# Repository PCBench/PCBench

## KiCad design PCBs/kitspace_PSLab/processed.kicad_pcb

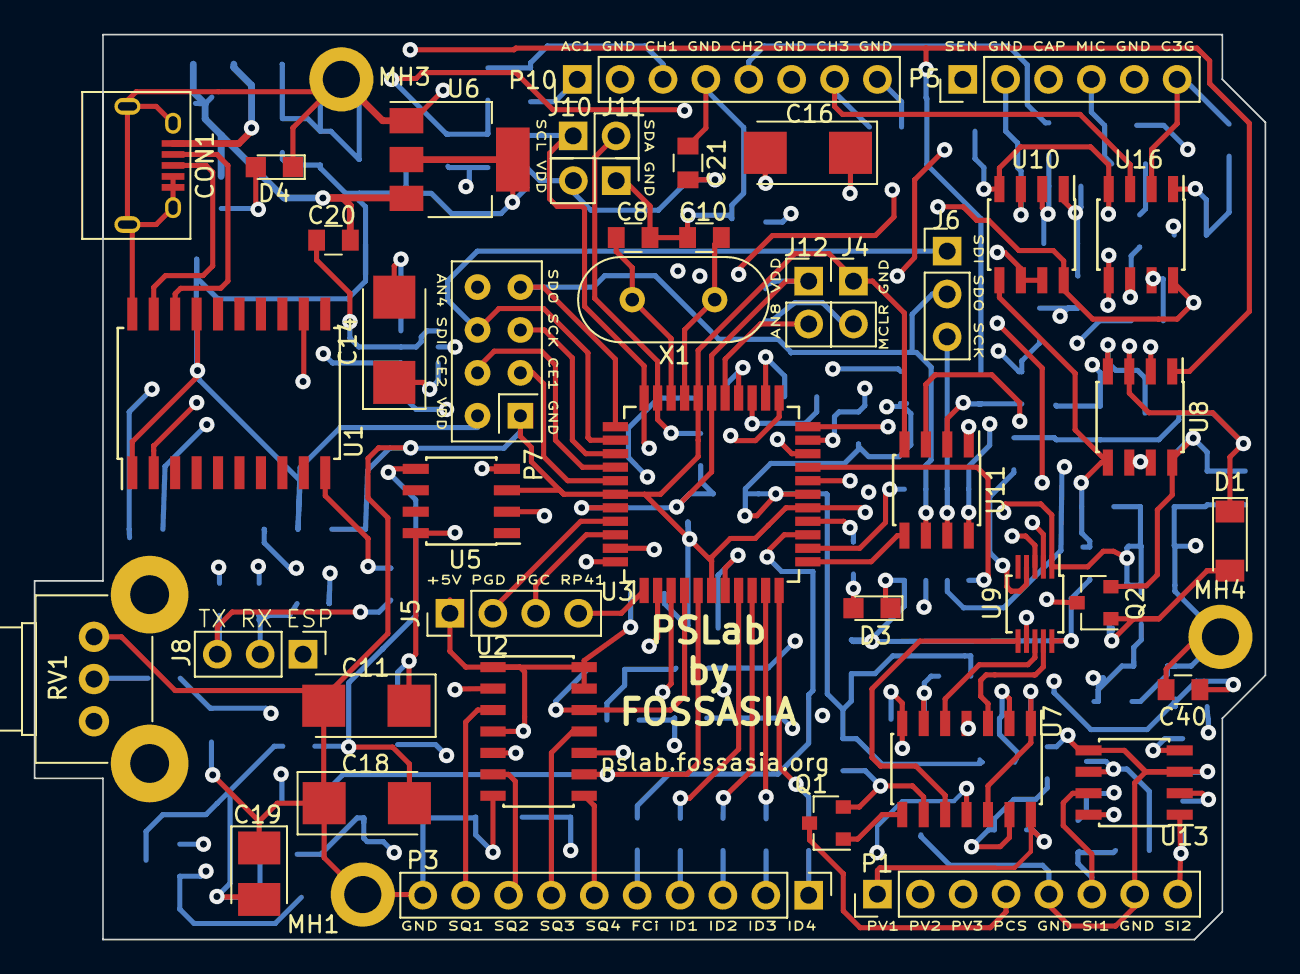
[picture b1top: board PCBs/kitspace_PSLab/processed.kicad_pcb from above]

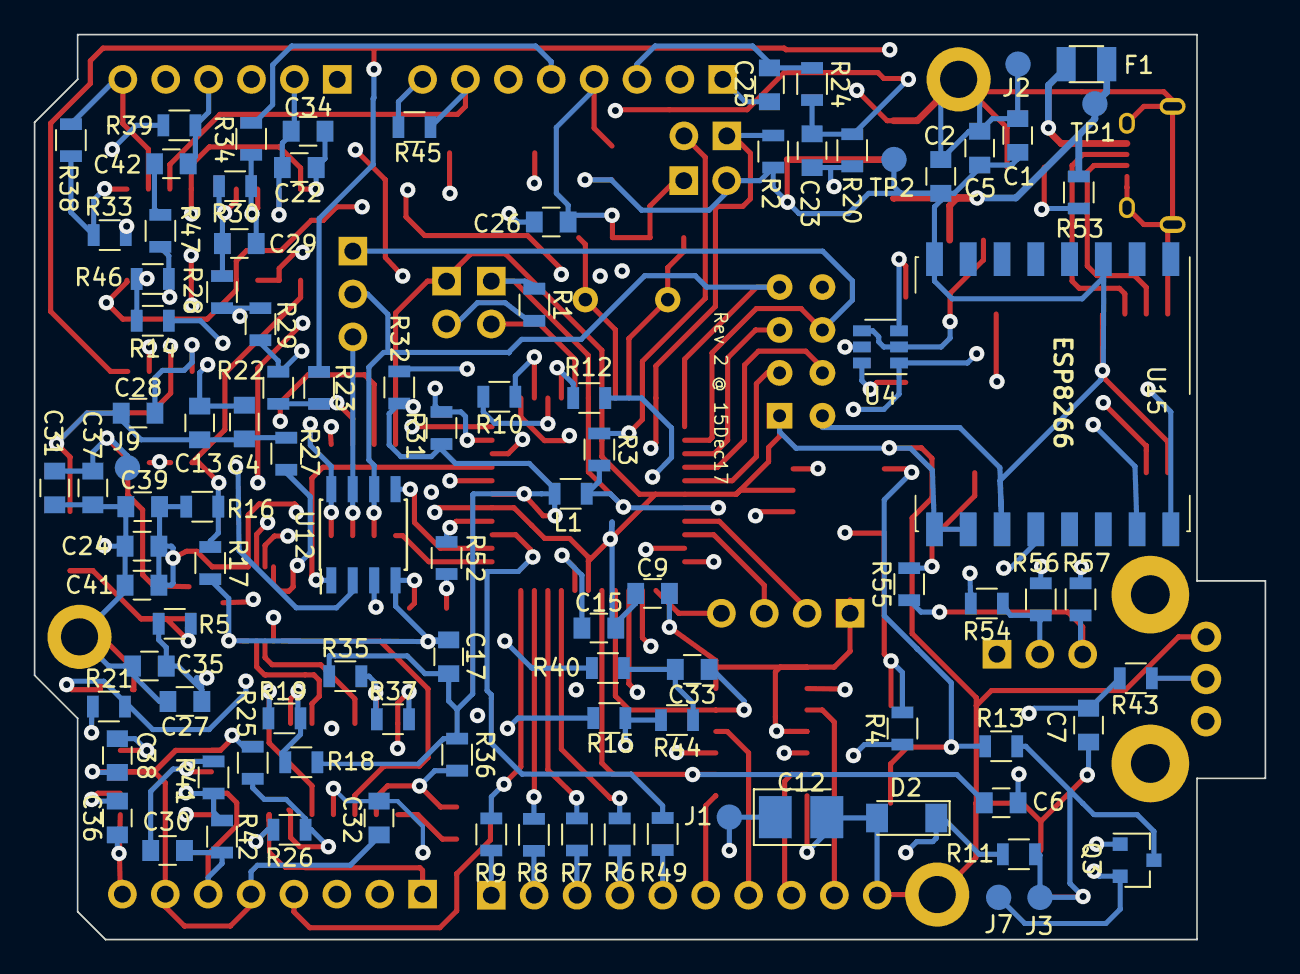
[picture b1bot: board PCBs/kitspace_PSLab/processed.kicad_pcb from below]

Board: 4 copper layers, 72.9 x 53.6 mm, 144 parts (99 on the bottom side), 114 nets.

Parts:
C1, C2, C4, C5, C9, C13, C17, C22, C24, C25, C26, C27, C28, C31, C32, C34, C35, C37, C38, C39, C41: 0.1u; C_0805
C6, C15, C21, C33: 10u; C_0805
C7, C40: 10nF; C_0805
C8, C10: 15pF; C_0805
C11, C14, C16, C18: 100u; CP_Tantalum_Case-C_EIA-6032-28_Reflow
C12, C19: 33u; CP_Tantalum_Case-B_EIA-3528-21_Reflow
C20, C42: 1u; C_0805
C23, C29: 3p3; C_0805
C30, C36: 1nF; C_0805
CON1: USB-MICRO-B; USB_Micro-B
D1, D2: 6V8; D_MiniMELF
D3, D4: LED; LED_0805
F1: 0.5A; Fuse_SMD1206_Reflow
J1: V+; Measurement_Point_Round-SMD-Pad_Small
J2: GND; Measurement_Point_Round-SMD-Pad_Small
J3: V-; Measurement_Point_Round-SMD-Pad_Small
J4: Ex-I; Pin_Header_Straight_1x02_Pitch2.54mm
J5: PG_Pins; Pin_Header_Straight_1x04_Pitch2.54mm
J6: Exp; Pin_Header_Straight_1x03_Pitch2.54mm
J7: VR-; Measurement_Point_Round-SMD-Pad_Small
J8: TX_RX_ES; Pin_Header_Straight_1x03_Pitch2.54mm
J9: VR+; Measurement_Point_Round-SMD-Pad_Small
J10: I2C-I; Pin_Header_Straight_1x02_Pitch2.54mm
J11: I2C-II; Pin_Header_Straight_1x02_Pitch2.54mm
J12: Ex-II; Pin_Header_Straight_1x02_Pitch2.54mm
L1: 10uH; L_0805
MH1, MH3, MH4: M; MountingHole_2.2mm_M2_ISO14580_Pad
P1: CONN_01X08; Pin_Header_Straight_1x08_Pitch2.54mm
P3: DIO; Pin_Header_Straight_1x10_Pitch2.54mm
P5: sen-cap; Pin_Header_Straight_1x06_Pitch2.54mm
P7: NRF; nRF24L01_Breakout_2
P10: Analog; Pin_Header_Straight_1x08_Pitch2.54mm
Q1, Q3: MMBT3906; SOT-23
Q2: MMBT3904; SOT-23
R1, R2, R3, R10, R14, R16, R17, R18, R19, R21, R22, R23, R25, R28, R29, R31, R32, R33, R35, R37, R38, R39, R42: 10K; R_0805
R4, R13, R54, R55, R56, R57: 18; R_0805
R5, R11, R27, R36, R47: 1K; R_0805
R6, R7, R8, R9: 200; R_0805
R12, R15, R26, R41, R43, R44, R52, R53: 5K1; R_0805
R20, R30, R40, R46: 200K; R_0805
R24, R34, R45: 1M; R_0805
R49: 560; R_0805
RV1: 47K; Potentiometer_Alps_RK09K_Vertical
TP1: 5V; Measurement_Point_Round-SMD-Pad_Small
TP2: Vdd; Measurement_Point_Round-SMD-Pad_Small
U1: MCP2200; SOIC-20W_7.5x12.8mm_Pitch1.27mm
U2: 74HC126; SOIC-14_3.9x8.7mm_Pitch1.27mm
U3: PIC24EP256GP204; TQFP-44_10x10mm_Pitch0.8mm
U4: TC1240A; SOT-23-6
U5: 7660; SOIC-8_3.9x4.9mm_Pitch1.27mm
U6: LM1117-3.3; SOT-223
U7: LM324; SOIC-14_3.9x8.7mm_Pitch1.27mm
U8, U10, U13, U16: TL082; SOIC-8_3.9x4.9mm_Pitch1.27mm
U9: MCP4728; MSOP-10_3x3mm_Pitch0.5mm
U11, U12: 6S21; SOIC-8_3.9x4.9mm_Pitch1.27mm
U15: ESP8266; Hopref_RFM9XW_SMD
X1: 12MHz; Crystal_HC49-U_Vertical

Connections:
12MHz: C8.2, U1.2, U3.31, X1.1
+5V: C9.2, C20.2, F1.2, J5.1, R53.2, TP1.1, U2.1, U2.4, U2.10, U2.13, U2.14, U4.1, U6.3
/CAP: P5.3, R10.1, U3.24
/D+: CON1.3, U1.19
/D-: CON1.2, U1.18
/ERxD: R56.1, U15.15
/ESPROG: J8.1, U15.12
/ETxD: R57.1, U15.16
/FCin: P3.5, R49.2
/I/O Processing/DAC1: U7.3, U9.9
/I/O Processing/DAC2: U7.5, U9.8
/I/O Processing/DAC4: U7.10, U9.6
/ID1: R6.2, U3.8
/ID2: R7.2, U3.9
/ID3: R8.2, U3.10
/ID4: R9.2, U3.11
/MCLR: J4.2, R1.2, U3.18
/MRxD: R54.2, U1.12
/MTxD: R55.2, U1.10
/RxD: J8.2, R54.1, R56.2, U3.43
/SEN: P5.1, R12.1, U3.26
/SQR1: P3.9, U2.3
/SQR2: P3.8, U2.6
/SQR3: P3.7, U2.11
/SQR4: P3.6, U2.8
/TxD: J8.3, R55.1, R57.2, U3.44
ACH1: C25.2, P10.1
AN4: P7.8, U3.23
AN8: J12.2, U3.27
AVdd: C17.2, C24.2, C39.2, C41.2, L1.1, R12.2, R16.2, R18.1, R22.2, R29.1, R31.2, R32.2, R35.1, R36.1, R39.2, U3.17, U9.1, U11.8, U12.8
CH1: C25.1, P10.3, R24.1
CH1out: U3.22, U11.1
CH2: P10.5, R34.1
CH2out: U3.19, U12.1
CH3: P10.7, R45.2, U16.3
CH3.GAIN: P5.6, R38.1, U16.2
CH3out: R32.1, R33.1, U3.20
CS.CH1: U3.12, U11.5
CS.CH2: U3.13, U12.5
CS.E1: P7.3, U3.38
CS.E2: P7.4, U3.37
GND: C1.2, C2.1, C4.2, C5.2, C7.2, C8.1, C9.1, C10.1, C11.2, C12.2, C13.1, C15.2, C17.1, C18.1, C19.1, C20.1, C21.2, C22.1, C24.1, C26.1, C27.2, C28.1, C31.1, C32.2, C34.1, C35.1, C37.1, C38.1, C39.1, C40.2, C41.1, CON1.4, CON1.5, CON1.6, D1.1, D2.2, D3.1, D4.1, J2.1, J4.1, J11.1, MH1.1, MH3.1, MH4.1, P1.5, P1.7, P3.10, P5.2, P5.5, P7.1, P10.2, P10.4, P10.6, P10.8, R17.2, R25.1, R27.2, R40.2, R45.1, RV1.1, U1.20, U2.7, U3.6, U3.16, U3.29, U3.39, U4.2, U4.4, U5.3, U6.1, U8.3, U9.10, U10.3, U11.4, U12.4, U13.3, U13.5, U15.9, U15.10, U16.5
MIC: C42.2, P5.4, R39.1
MICout: R14.1, R31.1, U3.21
unnamed: C6.2, RV1.3
unnamed: C7.1, R41.2, R42.1, R43.2
unnamed: C10.2, U3.30, X1.2
unnamed: C11.1, R4.2, U4.5, U5.8
unnamed: C14.1, U4.6
unnamed: C14.2, U4.3
unnamed: C15.1, U3.7
unnamed: C16.1, U5.2
unnamed: C16.2, U5.4
unnamed: C18.2, R13.2, U5.5
unnamed: C23.1, R20.1, R23.2, U8.1
unnamed: C23.2, R20.2, R24.2, U8.2
unnamed: C29.1, R28.1, R30.1, U10.1
unnamed: C29.2, R30.2, R34.2, U10.2
unnamed: C30.2, R41.1, U13.6
unnamed: C33.2, R40.1, R44.1
unnamed: C36.2, R15.1, U13.2
unnamed: C40.1, R15.2, R21.2, R44.2
unnamed: C42.1, R47.2
unnamed: CON1.1, F1.1
unnamed: D1.2, Q2.1, R5.2
unnamed: D2.1, Q3.1, R11.1
unnamed: D3.2, R52.1
unnamed: D4.2, R53.1
unnamed: P3.1, R9.1
unnamed: P3.2, R8.1
unnamed: P3.3, R7.1
unnamed: P3.4, R6.1
unnamed: Q1.1, U7.8
unnamed: Q1.2, R36.2, U7.9
unnamed: R10.2, U3.25
unnamed: R14.2, R46.2, U16.7
unnamed: R16.1, R17.1, U8.5, U10.5
unnamed: R18.2, R19.1, U7.2
unnamed: R19.2, U7.1, U7.12
unnamed: R22.1, R23.1, U11.2
unnamed: R25.2, R26.1, U7.13
unnamed: R27.1, U9.4
unnamed: R28.2, R29.2, U12.2
unnamed: R33.2, R38.2, U16.1
unnamed: R35.2, R37.1, U7.6
unnamed: R43.1, RV1.2
unnamed: R46.1, R47.1, U16.6
unnamed: R49.1, U3.14
unnamed: U2.2, U3.2
unnamed: U2.5, U3.3
unnamed: U10.6, U10.7, U12.3
unnamed: U8.6, U8.7, U11.3
PCS: P1.4, Q1.3
PGC2: J5.3, U3.42
PGD2: J5.2, U3.41
PVS1: P1.1, R26.2, U7.14
PVS2: P1.2, R37.2, U7.7
PVS3: P1.3, U9.7
RP41: J5.4, U3.1
RP147: R52.2, U3.15
SCK: J6.3, P7.5, U3.36, U11.7, U12.7
SCL: J10.1, R2.1, U3.33, U9.2
SDA: J10.2, R3.1, U3.32, U9.3
SDI: J6.1, P7.6, U3.35
SDO: J6.2, P7.7, U3.34, U11.6, U12.6
SINE1: C30.1, P1.6, R42.2, U13.7
SINE2: C36.1, P1.8, R21.1, U13.1
SQ3: C33.1, U2.12, U3.4
SQ4: C6.1, U2.9, U3.5
V+: C12.1, C27.1, C35.2, J1.1, Q2.3, R4.1, R5.1, U7.4, U13.8
V-: C19.2, C32.1, C38.2, J3.1, Q3.3, R11.2, R13.1, U7.11, U13.4
VR+: C26.2, C31.2, C37.2, J9.1, Q2.2, U8.8, U10.8, U16.8
VR-: C22.2, C28.2, C34.2, J7.1, Q3.2, U8.4, U10.4, U16.4
Vdd: C1.1, C2.2, C4.1, C5.1, C13.2, C21.1, J11.2, J12.1, L1.2, P7.2, R1.1, R2.2, R3.2, TP2.1, U1.1, U1.17, U3.28, U3.40, U6.2, U6.4, U15.3, U15.8, U15.11

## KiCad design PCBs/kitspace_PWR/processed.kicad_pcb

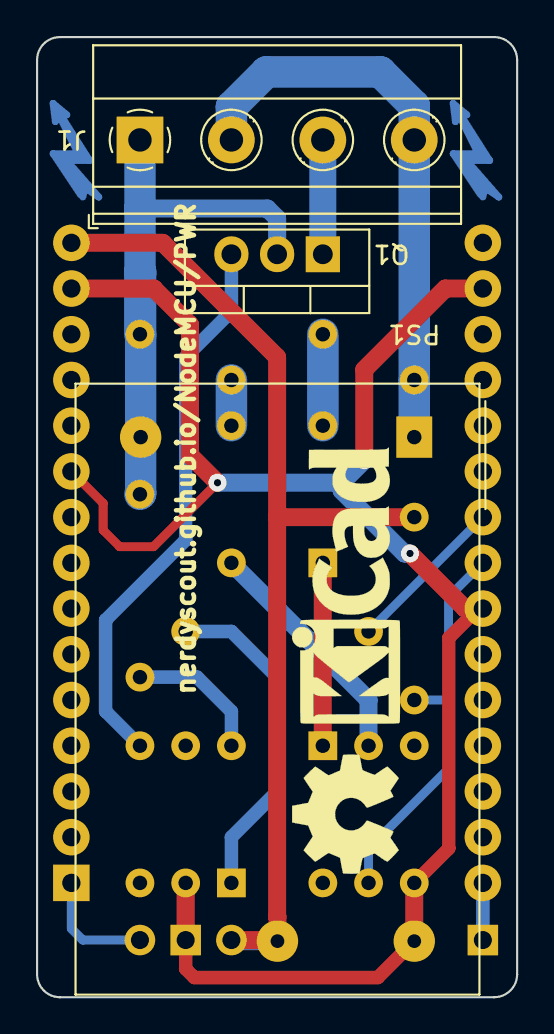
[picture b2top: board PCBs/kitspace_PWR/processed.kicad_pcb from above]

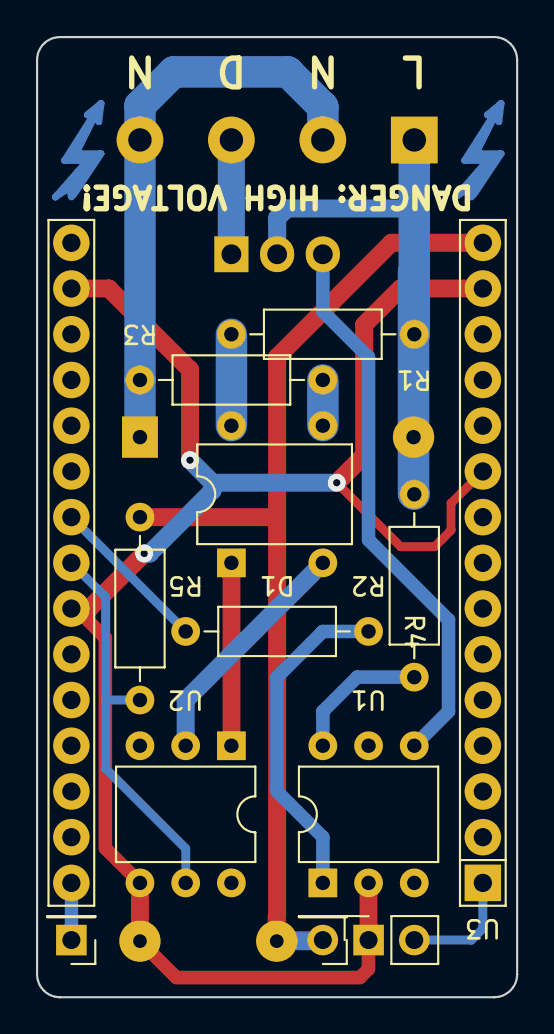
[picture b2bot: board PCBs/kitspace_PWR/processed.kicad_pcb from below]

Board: 2 copper layers, 26.7 x 53.3 mm, 19 parts (14 on the bottom side), 16 nets.

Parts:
D1: DF06M; Diode_Bridge_DIP-4_W7.62mm_P5.08mm
J1: Screw_Terminal_01x04; TerminalBlock_Phoenix_MKDS-1,5-4-5.08_1x04_P5.08mm_Horizont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
J2, J5: Conn_01x01; PinHeader_1x01_P2.54mm_Vertical
J3: Conn_01x02; PinSocket_1x02_P2.54mm_Vertical
LOGO1: Logo_Open_Hardware_Small; OSHW-Symbol_6.7x6mm_SilkScreen
LOGO2: Logo_Open_Hardware_Small; KiCad-Logo_6mm_SilkScreen
PS1: IRM-02-5; Converter_ACDC_MeanWell_IRM-02-xx_THT
Q1: TIC206; TO-220-3_Vertical
R1, R2, R3, R4, R5: R; R_Axial_DIN0207_L6.3mm_D2.5mm_P10.16mm_Horizontal
SYM1, SYM2: SYM_Flash_Small; Symbol_Highvoltage_Type1_CopperTop_Small
U1: MOC3021M; DIP-6_W7.62mm
U2: 4N25; DIP-6_W7.62mm
U3: NodeMCU1.0(ESP-12E); NodeMCU_Amica_WithMountingHoles

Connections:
+5V: J5.1, PS1.4, R5.2, U3.15
GND: J3.1, PS1.3, U1.2, U2.4, U3.10, U3.14, U3.17, U3.24
NEUT: J1.2, J1.4, PS1.1, R3.1
unnamed: D1.1, U2.1
unnamed: D1.2, U2.2
unnamed: D1.3, R3.2
unnamed: D1.4, R1.2
unnamed: J1.3, Q1.1
unnamed: J2.1, U3.30
unnamed: J3.2, U3.1
unnamed: Q1.3, U1.4
unnamed: R2.2, U1.6
unnamed: R4.1, U1.1
VAC: J1.1, PS1.2, Q1.2, R1.1, R2.1
dim: R4.2, U3.22
zero: R5.1, U2.5, U3.23

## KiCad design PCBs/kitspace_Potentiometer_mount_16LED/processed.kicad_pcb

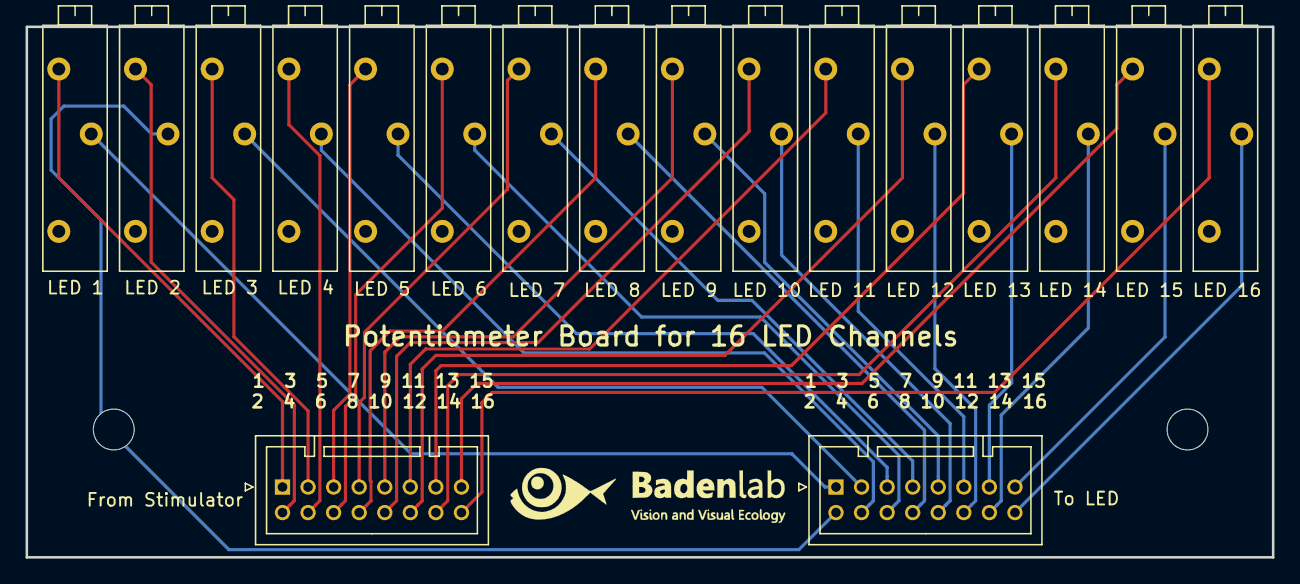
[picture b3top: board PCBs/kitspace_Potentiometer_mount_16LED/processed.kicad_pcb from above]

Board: 2 copper layers, 97.5 x 41.5 mm, 18 parts (0 on the bottom side), 32 nets.

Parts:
 LED 11: R_POT_TRIM; Potentiometer_Vishay_43_Horizontal
From Stimulator: JST_PUD_B16B-PUDSS_2x08_P2.00mm_Vertical
LED 1, LED 2, LED 3, LED 4: Potentiometer_Vishay_43_Horizontal
LED 5, LED 6, LED 7, LED 8, LED 9, LED 10, LED 12, LED 13, LED 14, LED 15, LED 16: R_POT_TRIM; Potentiometer_Vishay_43_Horizontal
To LED: JST_PUD_B16B-PUDSS_2x08_P2.00mm_Vertical

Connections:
unnamed: From Stimulator.1, LED 1.3
unnamed: From Stimulator.2, LED 2.3
unnamed: From Stimulator.3, LED 3.3
unnamed: From Stimulator.4, LED 4.3
unnamed: From Stimulator.5, LED 5.3
unnamed: From Stimulator.6, LED 6.3
unnamed: From Stimulator.7, LED 7.3
unnamed: From Stimulator.8, LED 8.3
unnamed: From Stimulator.9, LED 9.3
unnamed: From Stimulator.10, LED 10.3
unnamed: LED 11.3, From Stimulator.11
unnamed: From Stimulator.12, LED 12.3
unnamed: From Stimulator.13, LED 13.3
unnamed: From Stimulator.14, LED 14.3
unnamed: From Stimulator.15, LED 15.3
unnamed: From Stimulator.16, LED 16.3
unnamed: LED 1.2, To LED.1
unnamed: LED 2.2, To LED.2
unnamed: LED 3.2, To LED.3
unnamed: LED 4.2, To LED.4
unnamed: LED 5.2, To LED.5
unnamed: LED 6.2, To LED.6
unnamed: LED 7.2, To LED.7
unnamed: LED 8.2, To LED.8
unnamed: LED 9.2, To LED.9
unnamed: LED 10.2, To LED.10
unnamed: LED 11.2, To LED.11
unnamed: LED 12.2, To LED.12
unnamed: LED 13.2, To LED.13
unnamed: LED 14.2, To LED.14
unnamed: LED 15.2, To LED.15
unnamed: LED 16.2, To LED.16

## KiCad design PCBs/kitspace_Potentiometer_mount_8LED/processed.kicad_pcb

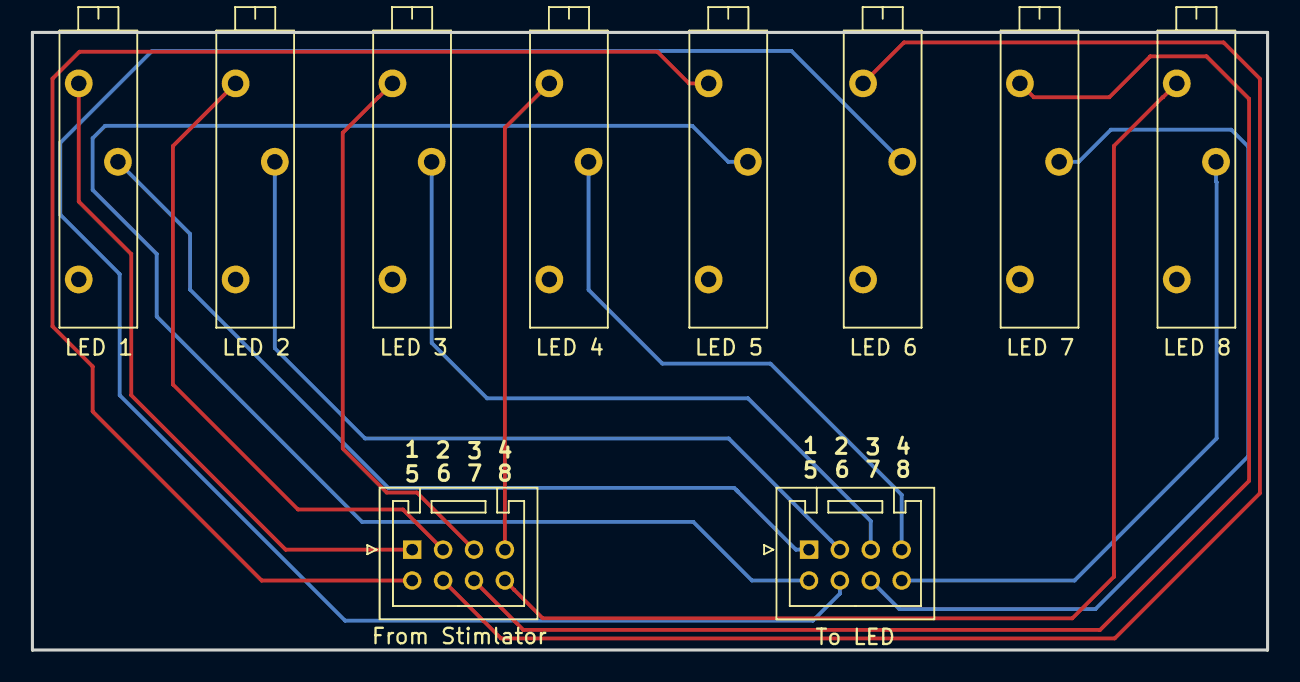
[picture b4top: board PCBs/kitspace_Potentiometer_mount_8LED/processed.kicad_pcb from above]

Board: 2 copper layers, 80.0 x 40.0 mm, 10 parts (0 on the bottom side), 8 nets.

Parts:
From Stimlator: JST_PUD_B08B-PUDSS_2x04_P2.00mm_Vertical
LED 1, LED 2, LED 3, LED 4, LED 5, LED 6, LED 7, LED 8: Potentiometer_Vishay_43_Horizontal
To LED: JST_PUD_B08B-PUDSS_2x04_P2.00mm_Vertical

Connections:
unnamed: From Stimlator.1, LED 1.3
unnamed: From Stimlator.3, LED 2.3
unnamed: From Stimlator.5, LED 3.3
unnamed: From Stimlator.7, LED 4.3
unnamed: LED 1.2, To LED.1
unnamed: LED 2.2, To LED.3
unnamed: LED 3.2, To LED.5
unnamed: LED 4.2, To LED.7

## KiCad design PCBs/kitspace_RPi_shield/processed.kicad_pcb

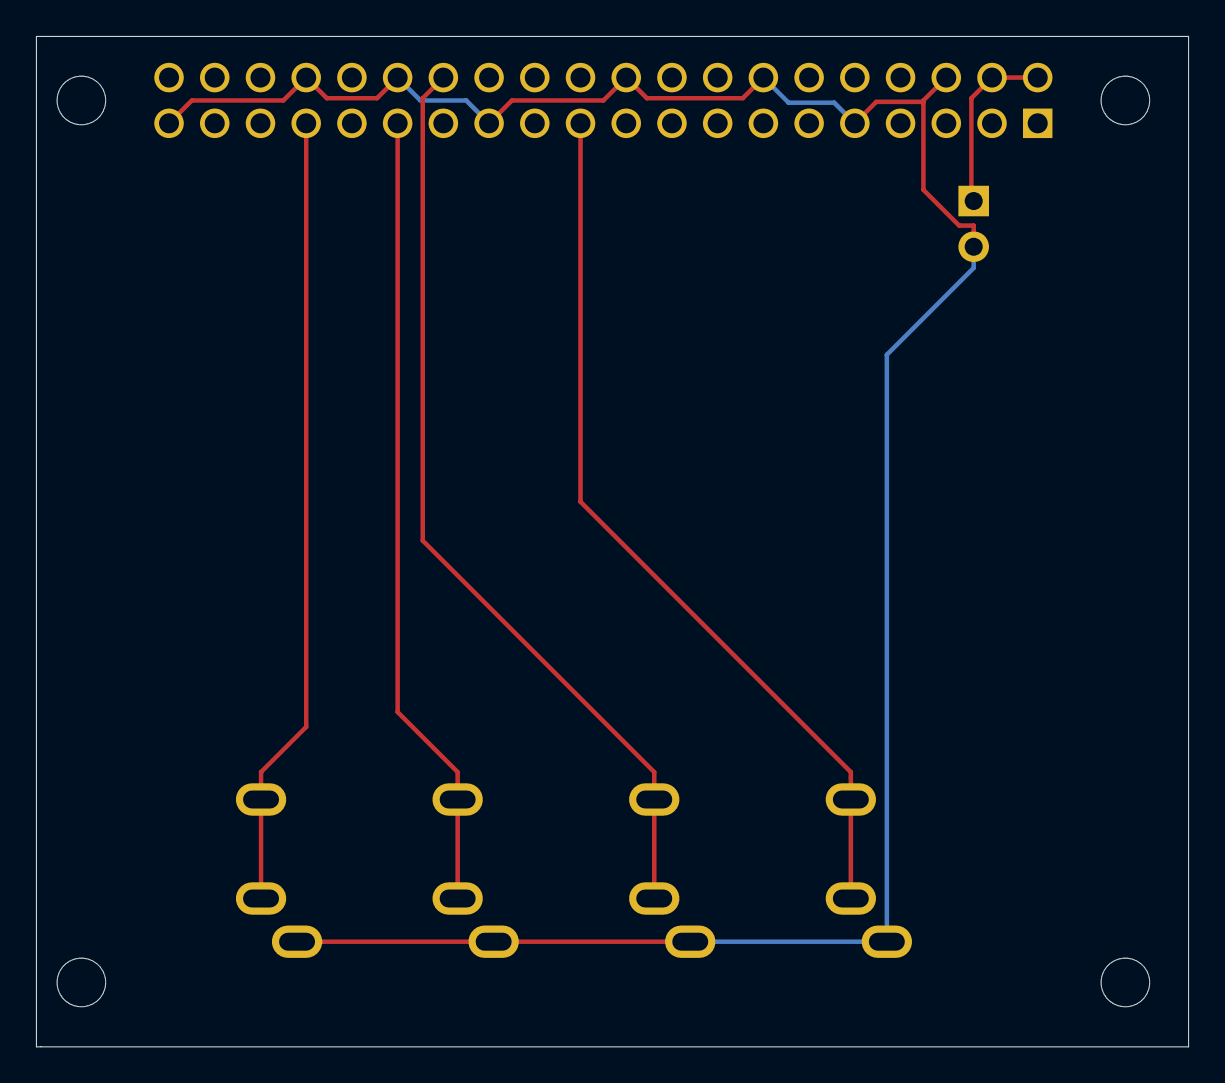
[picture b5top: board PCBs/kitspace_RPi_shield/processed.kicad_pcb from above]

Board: 2 copper layers, 64.0 x 56.1 mm, 6 parts (0 on the bottom side), 6 nets.

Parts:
J1, J2, J3, J4: AudioJack3; Jack_3.5mm_CUI_SJ1-3533NG_Horizontal
J5: RASPBERRY_PI_4B_+_Samtec_ESP-120-33-G-D; RASPBERRYPI4B4GB
M1: Fan; PinHeader_1x02_P2.54mm_Horizontal

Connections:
+5V: J5.2, J5.4, M1.1
GND: J1.S, J2.S, J3.S, J4.S, J5.6, J5.9, J5.14, J5.20, J5.25, J5.30, J5.34, J5.39, M1.2
jack1: J3.R, J3.T, J5.28
jack2: J2.R, J2.T, J5.29
jack3: J1.R, J1.T, J5.21
jack4: J4.R, J4.T, J5.33

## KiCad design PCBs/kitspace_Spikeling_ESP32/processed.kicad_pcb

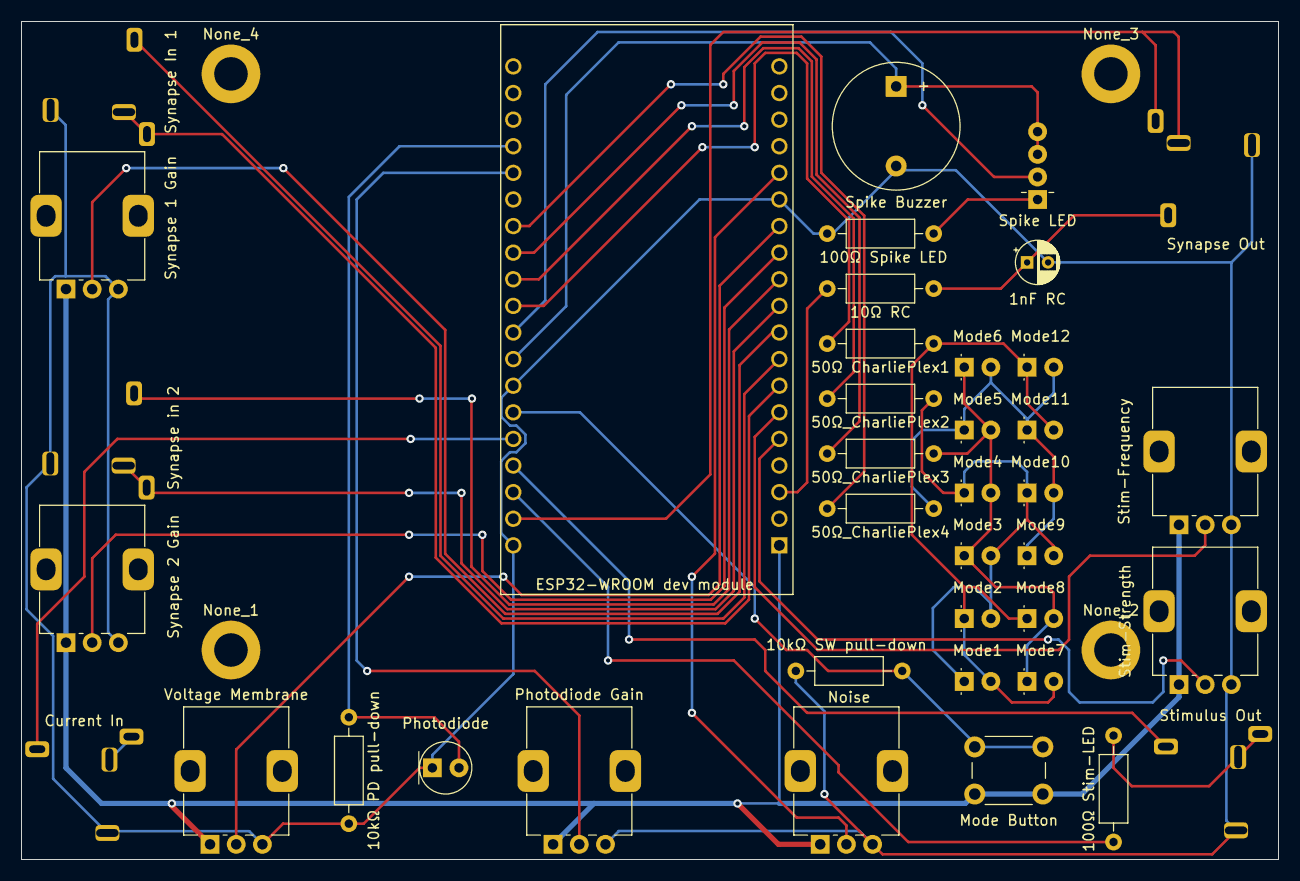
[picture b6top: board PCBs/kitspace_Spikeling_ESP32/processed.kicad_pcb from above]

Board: 2 copper layers, 120.0 x 80.0 mm, 43 parts (0 on the bottom side), 33 nets.

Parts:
1nF RC: C1; CP_Radial_D4.0mm_P2.00mm
10kΩ PD pull-down: R2; R_Axial_DIN0207_L6.3mm_D2.5mm_P10.16mm_Horizontal
10kΩ SW pull-down: R5; R_Axial_DIN0207_L6.3mm_D2.5mm_P10.16mm_Horizontal
10Ω RC: R1; R_Axial_DIN0207_L6.3mm_D2.5mm_P10.16mm_Horizontal
50Ω CharliePlex1: R6; R_Axial_DIN0207_L6.3mm_D2.5mm_P10.16mm_Horizontal
50Ω_CharliePlex2: R7; R_Axial_DIN0207_L6.3mm_D2.5mm_P10.16mm_Horizontal
50Ω_CharliePlex3: R8; R_Axial_DIN0207_L6.3mm_D2.5mm_P10.16mm_Horizontal
50Ω_CharliePlex4: R9; R_Axial_DIN0207_L6.3mm_D2.5mm_P10.16mm_Horizontal
100Ω Spike LED: R4; R_Axial_DIN0207_L6.3mm_D2.5mm_P10.16mm_Horizontal
100Ω Stim-LED: R3; R_Axial_DIN0207_L6.3mm_D2.5mm_P10.16mm_Horizontal
Current In: J4; Audio Jack 3.5mm
ESP32-WROOM dev module: ESP32-DEVKITC-32D; MODULE_ESP32-DEVKITC-32D
Mode1: D2; LED_D3.0mm
Mode2: D3; LED_D3.0mm
Mode3: D4; LED_D3.0mm
Mode4: D5; LED_D3.0mm
Mode5: D6; LED_D3.0mm
Mode6: D7; LED_D3.0mm
Mode7: D8; LED_D3.0mm
Mode8: LED; LED_D3.0mm
Mode9: D10; LED_D3.0mm
Mode10: D11; LED_D3.0mm
Mode11: D12; LED_D3.0mm
Mode12: D13; LED_D3.0mm
Mode Button: SW1; SW_PUSH_6mm_H13mm
Noise: RV4; Potentiometer_Alps_RK09K_Single_Vertical
None_1, None_2, None_3, None_4: MountingHole_3.2mm_M3_DIN965_Pad
Photodiode: D1; LED_D5.0mm
Photodiode Gain: RV5; Potentiometer_Alps_RK09K_Single_Vertical
Spike Buzzer: BZ1; Buzzer_12x9.5RM7.6
Spike LED: RGB; LED_D5.0mm-4_RGB_Wide_Pins
Stim-Frequency: RV7; Potentiometer_Alps_RK09K_Single_Vertical
Stim-Strength: RV6; Potentiometer_Alps_RK09K_Single_Vertical
Stimulus Out: J5; Audio Jack 3.5mm
Synapse 1 Gain: RV1; Potentiometer_Alps_RK09K_Single_Vertical
Synapse 2 Gain: RV2; Potentiometer_Alps_RK09K_Single_Vertical
Synapse In 1: J2; Audio Jack 3.5mm
Synapse Out: J1; Audio Jack 3.5mm
Synapse in 2: J3; Audio Jack 3.5mm
Voltage Membrane: RV3; Potentiometer_Alps_RK09K_Single_Vertical

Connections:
+3V3: ESP32-WROOM dev module.1, Mode Button.2, Noise.1, Photodiode Gain.1, Stim-Frequency.1, Stim-Strength.1, Synapse 1 Gain.1, Synapse 2 Gain.1, Voltage Membrane.1
/01: ESP32-WROOM dev module.23, Stimulus Out.R
/02: ESP32-WROOM dev module.34, Photodiode Gain.2
/03: Current In.R, ESP32-WROOM dev module.24
/04: 50Ω_CharliePlex4.1, ESP32-WROOM dev module.32
/05: 50Ω CharliePlex1.1, ESP32-WROOM dev module.29
/12: ESP32-WROOM dev module.13, Voltage Membrane.2
/13: ESP32-WROOM dev module.15, Noise.2
/14: ESP32-WROOM dev module.12, Synapse 2 Gain.2
/15: 10kΩ PD pull-down.1, ESP32-WROOM dev module.35, Photodiode.2
/16: 50Ω_CharliePlex3.1, ESP32-WROOM dev module.31
/17: 50Ω_CharliePlex2.1, ESP32-WROOM dev module.30
/18: ESP32-WROOM dev module.28, Spike LED.2
/19: ESP32-WROOM dev module.27, Spike Buzzer.1, Spike LED.3, Spike LED.4
/21: 10kΩ SW pull-down.1, ESP32-WROOM dev module.25, Mode Button.1
/22: 100Ω Stim-LED.1, ESP32-WROOM dev module.22
/23: ESP32-WROOM dev module.21, Synapse Out.T
/25: ESP32-WROOM dev module.9, Synapse 1 Gain.2
/26: ESP32-WROOM dev module.10, Synapse in 2.T
/27: ESP32-WROOM dev module.11, Synapse in 2.R
/32: ESP32-WROOM dev module.7, Synapse In 1.T
/33: ESP32-WROOM dev module.8, Synapse In 1.R
/34: ESP32-WROOM dev module.5, Stim-Strength.2
/35: ESP32-WROOM dev module.6, Stim-Frequency.2
/36: 10Ω RC.1, ESP32-WROOM dev module.3
GNDREF: 1nF RC.2, 10kΩ PD pull-down.2, 10kΩ SW pull-down.2, 100Ω Spike LED.1, Current In.S, ESP32-WROOM dev module.14, ESP32-WROOM dev module.20, ESP32-WROOM dev module.26, Noise.3, Photodiode.1, Photodiode Gain.3, Spike Buzzer.2, Stim-Frequency.3, Stim-Strength.3, Stimulus Out.S, Synapse 1 Gain.3, Synapse 2 Gain.3, Synapse In 1.S, Synapse Out.S, Synapse in 2.S, Voltage Membrane.3
unnamed: 1nF RC.1, 10Ω RC.2, Synapse Out.R
unnamed: 50Ω CharliePlex1.2, Mode1.2, Mode2.1, Mode7.2, Mode8.1, Mode11.2, Mode12.1
unnamed: 50Ω_CharliePlex2.2, Mode1.1, Mode2.2, Mode3.2, Mode4.1, Mode9.2, Mode10.1
unnamed: 50Ω_CharliePlex3.2, Mode3.1, Mode4.2, Mode5.2, Mode6.1, Mode7.1, Mode8.2
unnamed: 50Ω_CharliePlex4.2, Mode5.1, Mode6.2, Mode9.1, Mode10.2, Mode11.1, Mode12.2
unnamed: 100Ω Spike LED.2, Spike LED.1
unnamed: 100Ω Stim-LED.2, Stimulus Out.T

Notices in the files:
PCBs/kitspace_RPi_shield/processed.kicad_pcb:
CERN OHL-S v2.0
